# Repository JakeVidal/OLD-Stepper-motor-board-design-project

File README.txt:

This project is a PCB designed in KICAD that allows an arduino to easily operate a 6-wire stepper motor drive. The board requires a clock to modulate the motor speed, and a direction as inputs.

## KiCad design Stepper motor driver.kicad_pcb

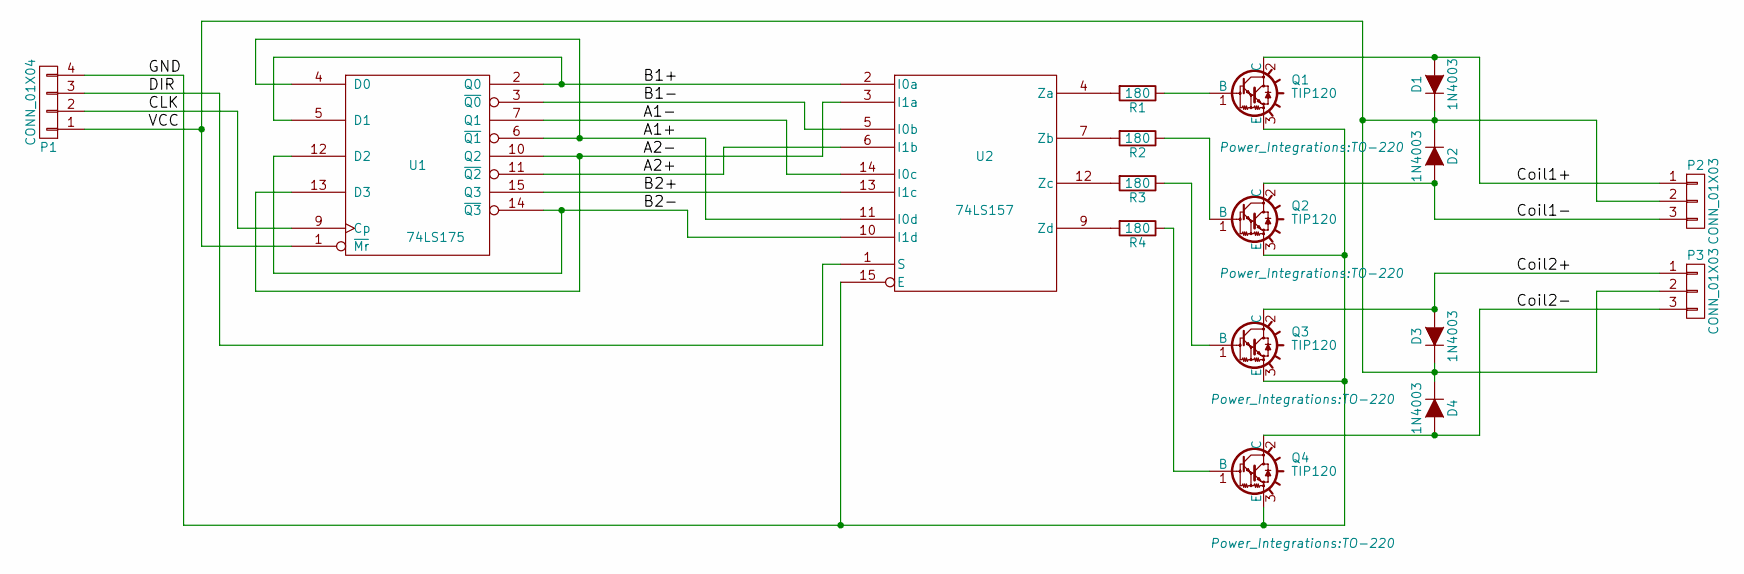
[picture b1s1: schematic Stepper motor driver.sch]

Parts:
D1, D2, D3, D4: 1N4003; D_DO-35_SOD27_P7.62mm_Horizontal
P1: CONN_01X04; Pin_Header_Straight_1x04_Pitch1.27mm
P2, P3: CONN_01X03; Pin_Header_Straight_1x03_Pitch1.27mm
Q1, Q2, Q3, Q4: TIP120; TO-220
R1, R2, R3, R4: 180; R_1206_HandSoldering
U1: 74LS175; SO-16-N
U2: 74LS157; SO-16-N

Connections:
/A1+: U1.4 (D0), U1.6 (~Q1), U2.11 (I0d)
/A1-: U1.7 (Q1), U2.14 (I0c)
/A2+: U1.11 (~Q2), U2.6 (I1b)
/A2-: U1.10 (Q2), U1.13 (D3), U2.3 (I1a)
/B1+: U1.2 (Q0), U1.5 (D1), U2.2 (I0a)
/B1-: U1.3 (~Q0), U2.5 (I0b)
/B2+: U1.15 (Q3), U2.13 (I1c)
/B2-: U1.12 (D2), U1.14 (~Q3), U2.10 (I1d)
/CLK: P1.2, U1.9 (Cp)
/Coil1+: D1.2 (A), P2.1, Q1.2 (C)
/Coil1-: D2.2 (A), P2.3, Q2.2 (C)
/Coil2+: D3.2 (A), P3.1, Q3.2 (C)
/Coil2-: D4.2 (A), P3.3, Q4.2 (C)
/DIR: P1.3, U2.1 (S)
GND: P1.4, Q1.3 (E), Q2.3 (E), Q3.3 (E), Q4.3 (E), U1.8 (GND), U2.8 (GND), U2.15 (E)
unnamed: Q1.1 (B), R1.1
unnamed: Q2.1 (B), R2.1
unnamed: Q3.1 (B), R3.1
unnamed: Q4.1 (B), R4.1
unnamed: R1.2, U2.4 (Za)
unnamed: R2.2, U2.7 (Zb)
unnamed: R3.2, U2.12 (Zc)
unnamed: R4.2, U2.9 (Zd)
VCC: D1.1 (K), D2.1 (K), D3.1 (K), D4.1 (K), P1.1, P2.2, P3.2, U1.1 (~Mr), U1.16 (VCC), U2.16 (VCC)

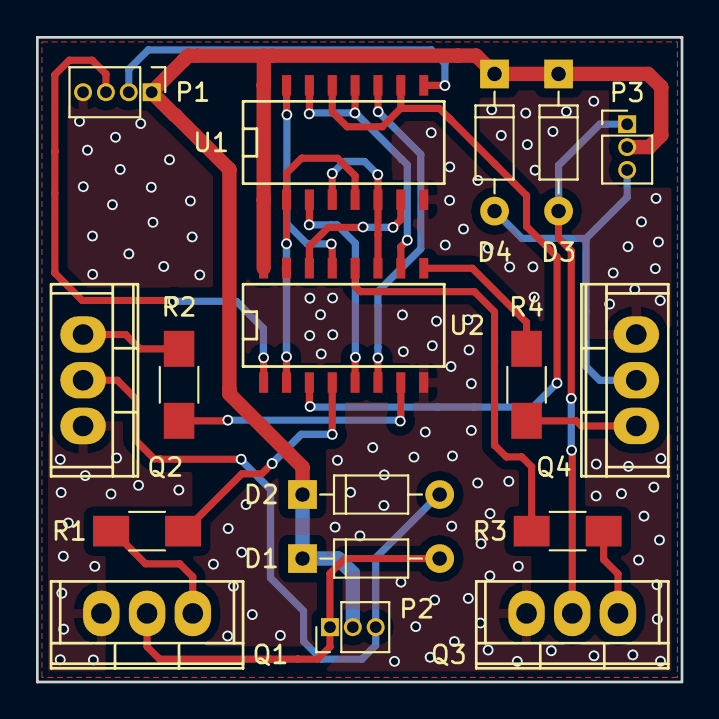
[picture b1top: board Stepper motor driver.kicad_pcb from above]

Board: 2 copper layers, 35.8 x 35.8 mm, 17 parts (0 on the bottom side), 24 nets.

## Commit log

2016-04-27 finished schematic, started PCB routing
2016-04-29 finished PCB initial routing
2016-04-29 fixed schematic and finished all routing
2016-04-29 finished PCB completely, added gerber files and picture of layout
2016-04-29 fixed minor silkscreen error
2016-05-01 touched up schematic and PCB, added ground pour, updated gerber and image files
2016-05-03 added a second ground layer to distribute current
2016-05-03 added additional vias
2017-02-22 Added connectors for I/O and changed to SMD components
2017-02-23 Cleaned up schematic and placed PCB components
2017-02-24 Small schematic change, fine component placement, silkscreen
2017-02-25 Added VCC to output, initial board routing
2017-02-25 Continued routing progress
2017-02-26 Updated todo and readme files
2017-02-26 Updated project file
2017-02-27 Completed initial routing
2017-02-27 Moved input connector
2017-02-28 Added gitignore file
2017-02-28 Removed ignored files
2017-03-29 Refined traces to improve ground plane coverage
2017-03-30 Finished final trace routing
2017-03-31 Finished ground plane and updated images
2017-04-01 Added vias to connect ground planes
2017-04-02 Finished silkscreen and exported gerber files
2017-04-09 Updated todo file
